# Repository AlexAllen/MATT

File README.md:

# Overview

MATT stands for "Multifunction Altimeter with Telemetry and Tracking", and is a DIY flight computer project that aims to tick several boxes in the [United Kingdom Rocketry Association's (UKRA) Model Achievement Program (MAP)](https://ukra.org.uk/certification/model-achievement-programme/). I have already done the DIY altimeter task, using an Arduino and breakout boards on stripboard, as recorded in [my rocket altimeter repo](https://github.com/AlexAllen/rocket_altimeter), and this project intends to produce something that can tick all of the remaining MAP tasks that require a custom altimeter:

* DIY flight computer
	* Details are light on the exact requirements, but I'm assuming a typical dual deploy flight computer
* Satellite
	* A cansat which records some physical data and transmits it back to the ground at 1Hz.
* Land under thrust
	* Need to be able to control servos for thrust vectoring

I also want to use this project as a vehicle for learning about PCB design, and to improve my electronics skills more generally. I intend to use a microcontroller board (maybe a Pico of some sort, or a Teensy) as a starting point, and then to create my own PCB to provide the rest of the functionality I require. I might do this in stages, creating some simpler boards with a subset of the final functionality on the way towards the final board. 

While the resulting flight computer will be overkill for any of these applications, as I don't expect space or weight contraints to be an issue for any of the flights (within reason), having them all use the same computer (or at least a subset of the same computer) means that every flight can help collect data and test functionality for each of the other applications. If I subsequently find I want a more compact, focussed flight computer for a specific application, then that can be its own project, building on the experience gained here. 

---------------------

# Requirements

1. Must have Mach safe two channel (apogee and main) deployment triggered off pressure data
	* Required to meet DIY flight computer task definition
1. Must have buzzer for audible altimeter arming alerts
	* Required for safety when completing DIY flight computer task
1. Must record flight data in a robust way in flight (not to an SD card!), and make the data retrievable afterwards
	* Will make the result more useful, and make it easier to test
1. Could have individual wireless test functionality for both deployment channels
	* Makes the result more flexible, but could be a later update
1. Must have UK legal radio link capable of transmitting recorded data at 1Hz
	* Required to meet Satellite task definition
1. Must record temperature data as well as pressure data, for transmission
	* Required for Satellite task
1. Should transmit on a frequency and in a format that can be picked up by an eggtimer USB ground station
	* Allows reuse of existing equiment
1. Must have enough PWM outputs to control a thrust vectoring mount and deploy legs
	* Required to meet the Land under thrust task task definition
1. Should have enough PWM outputs to control 4 canards instead of thrust vectoring and legs
	* Makes the result more future proof
1. Must have accelerometers and gyroscopes
	* Required to complete the Land under thrust task 
1. Should have magnetometers
	* Makes the result more flexible
1. Should have a GPS module, and be able to transmit as a GPS tracking radio
	* Makes the result more useful, given an onboard radio is required already
	
---------------------

# Potential chips/ boards to investigate

## Microcontroller

### Pimoroni Pico 2 Plus W / Pico LiPo 2 XL W

The Pico 2 Plus W was my starting point before I started looking at the Teensy alternatives. I already have some, and have used them at least a little, so that's a plus in their favour. They also either come with, or have options for coming with, some features I want already built in. This includes wifi, and some lipo functionality. It also has bluetooth, if I want to use that instead of wifi. 

The Pico LiPo 2 XL W has the lipo functionality built in already, and is longer as a result (76mm vs 51mm), but also comes with more pins. They are both 21mm wide.

Useful links:

* [Pimoroni Pico 2 Plus W](https://shop.pimoroni.com/products/pimoroni-pico-plus-2-w?variant=42182811942995)
* [Pimoroni LiPo Shim](https://shop.pimoroni.com/products/pico-lipo-shim?variant=32369543086163)
* [Pimoroni Pico LiPo 2 XL W](https://shop.pimoroni.com/products/pimoroni-pico-lipo-2-xl-w?variant=55447911006587)

### Teensy 4.0 or 4.1

This looks to have a significantly more powerful processor than a pico plus 2, and hardware floating point calculations, so I'll have plenty of grunt for calculations, but have to do more stuff myself (wifi, etc). The Teensy 4.1 is a larger and more fully featured board than the Teensy 4.0, at about 61mm vs 36mm (both are about 18mm wide). The 4.1 has the option to add 2x 8MB QSPI chips directly onto the board, and a built in microSD card reader, so I could look at writing some data storage/ retrival code before the PCB is complete.

Useful links:

* [Pi Hut Teensy 4.1](https://thepihut.com/products/teensy-4-1)
* [Pimoroni Teensy 4.1](https://shop.pimoroni.com/products/teensy-4-1?variant=31757218250835)
* [Teensy 4.1 documentation](https://www.pjrc.com/store/teensy41.html)

Or:

* [Pi Hut Teensy 4.0](https://thepihut.com/products/pjrc-teensy-4-0-usb-development-board)
* [Pimoroni Teensy 4.0](https://shop.pimoroni.com/products/teensy-4-0-development-board?variant=29443577217107)
* [Teensy 4.0 documentation](https://www.pjrc.com/store/teensy40.html)

## RF modules

### ESP8266-12 WiFi Module

If I go for the Teensy over the pico, then I don't get wifi built in. This is the wifi module that eggtimer uses.

### Hope RF HM-TRP-868 RF module

This is the one used by eggtimer, so should be compatible with the ground station. There is also an otherwise identical 433 MHz version, which may be useful later.

## Sensors

### BMP 390 (or 388, or 280, or ...)

A temperature and pressure sensor. I used the BMP 280 on my [rocket altimeter](https://github.com/AlexAllen/rocket_altimeter) with good results, and I have one on a breakout board to play with already. According to the Adafruit overview, the BMP280 has a relative accuracy of 12 Pa, the BMP388 8 Pa, and the BMP390 3 Pa. That translates to about 1m for the BMP280 or about 0.25m for the BMP390. Seems to be recommended on TRF threads about building flight computers, so this is probably the one to go for.

### LSM6DSV80X 

A two channel accelerometer, with gyroscope. 16g and 80g should cover most foreseeable use cases. The LSM6DSO32 or similar seem to be recommended on TRF, but this looks like an updated version that includes an 80g rather than a 32g high range accelerometer.

### LIS3MDL

This magnetometer is discussed on [TRF](https://www.rocketryforum.com/threads/magnetometer-calibration.193930/), but seems to be unavailable.

### LIS2MDLTR

This does appear to be available.

### Quectel L80-R

I have some of these, somewhere. Which is a big point in their favour!

### Something from ublox?

People seem to rate these highly, might be worth investigating

## Other

### VN5E160STR-E

These are what the eggtimer quark uses to control deployment charges. According to Cris Erving of Eggtimer Rocketry, ["in one SOIC-8 package you get 10A current limiting, continuity checking, brownout protection (it shuts off the load if the input voltage drops below 4.5V), overtemperature protection, and they will work with up to 40V input."](https://www.rocketryforum.com/threads/flight-computer-schematic-review-request.186506/post-2588670).

### W25Q01JVZEIM 

1 gigabit flash, so could store plenty of flight data, and recover it later, even after power off.

### Pololu D30V30MAL

Looks like a very capable buck converter.
	
---------------------

# Other useful things:

### Ulyu (Silicdyne) talks about how to implement an IMU

[This thread on TRF](https://www.rocketryforum.com/threads/did-any-one-found-out-a-way-to-calculate-the-velocity-and-altitude-using-imu-sensors-with-practical-code.191467/post-2722289)

### Cris Erving (Eggtimer) suggests owning this book

[The Circuit Designer's Companion](https://www.amazon.co.uk/Circuit-Designers-Companion-Wilson-Professor/dp/0081017642)

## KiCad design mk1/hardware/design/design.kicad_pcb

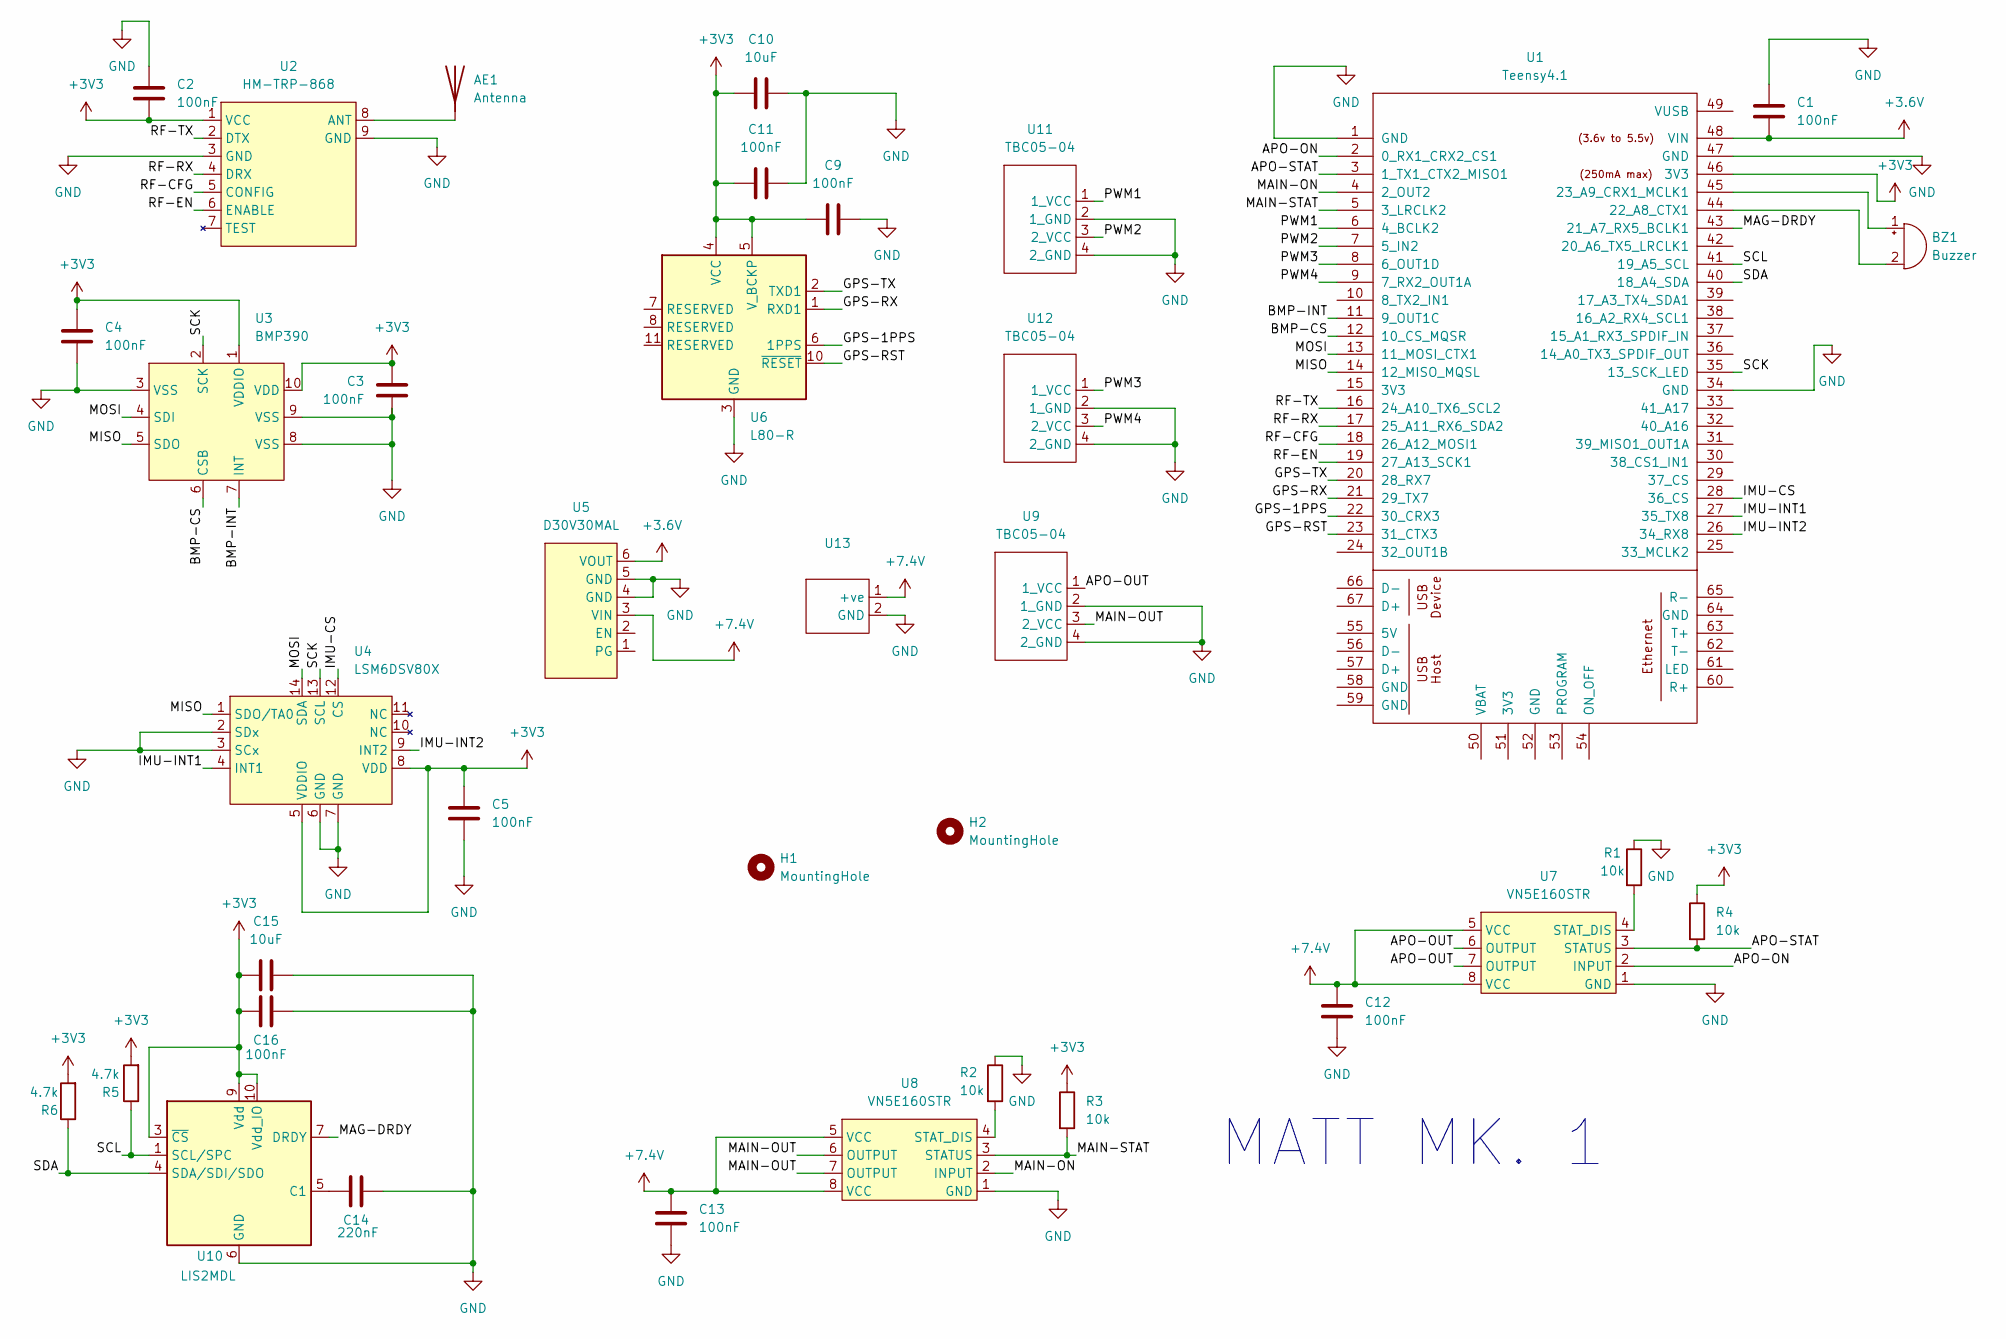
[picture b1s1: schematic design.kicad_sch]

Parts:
AE1: Antenna; ANT-868-PW
BZ1: Buzzer; AX1203DLF
C1, C2, C3, C4, C5, C9, C11, C12, C13, C16: 100nF; C_0805_2012Metric_Pad1.18x1.45mm_HandSolder
C10, C15: 10uF; C_0805_2012Metric_Pad1.18x1.45mm_HandSolder
C14: 220nF; C_0805_2012Metric_Pad1.18x1.45mm_HandSolder
H1, H2: MountingHole; MountingHole_2.7mm_M2.5
R1, R2, R3, R4: 10k; R_0805_2012Metric_Pad1.20x1.40mm_HandSolder
R5, R6: 4.7k; R_0805_2012Metric_Pad1.20x1.40mm_HandSolder
U1: Teensy4.1; teensy4.1
U2: HM-TRP-868; HM-TRP-XXX
U3: BMP390
U4: LSM6DSV80X
U5: D30V30MAL; D30V30MAx
U6: L80-R; Quectel_L80-R
U7, U8: VN5E160STR; vn5e160s
U9: TBC05-04; TBC05-04_charges
U10: LIS2MDL; LGA-12_2x2mm_P0.5mm
U11: TBC05-04; TBC05-04_pwm1
U12: TBC05-04; TBC05-04_pwm2
U13: power_in

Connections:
+3.6V: C1.1, U1.48 (VIN), U5.6 (VOUT)
+3V3: C2.2, C3.1, C4.1, C5.1, C9.2, C10.2, C11.2, C15.1, C16.2, R3.1, R4.1, R5.2, R6.2, U1.46 (3V3), U2.1 (VCC), U3.1 (VDDIO), U3.10 (VDD), U4.5 (VDDIO), U4.8 (VDD), U6.4 (VCC), U6.5 (V_BCKP), U10.3 (~CS), U10.9 (Vdd), U10.10 (Vdd_IO)
+7.4V: C12.1, C13.1, U5.3 (VIN), U7.5 (VCC), U7.8 (VCC), U8.5 (VCC), U8.8 (VCC), U13.1 (+ve)
/APO-ON: U1.2 (0_RX1_CRX2_CS1), U7.2 (INPUT)
/APO-OUT: U7.6 (OUTPUT), U7.7 (OUTPUT), U9.1 (1_VCC)
/APO-STAT: R4.2, U1.3 (1_TX1_CTX2_MISO1), U7.3 (STATUS)
/BMP-CS: U1.12 (10_CS_MQSR), U3.6 (CSB)
/BMP-INT: U1.11 (9_OUT1C), U3.7 (INT)
/GPS-1PPS: U1.22 (30_CRX3), U6.6 (1PPS)
/GPS-RST: U1.23 (31_CTX3), U6.10 (~RESET)
/GPS-RX: U1.21 (29_TX7), U6.1 (RXD1)
/GPS-TX: U1.20 (28_RX7), U6.2 (TXD1)
/IMU-CS: U1.28 (36_CS), U4.12 (CS)
/IMU-INT1: U1.27 (35_TX8), U4.4 (INT1)
/IMU-INT2: U1.26 (34_RX8), U4.9 (INT2)
/MAG-DRDY: U1.43 (21_A7_RX5_BCLK1), U10.7 (DRDY)
/MAIN-ON: U1.4 (2_OUT2), U8.2 (INPUT)
/MAIN-OUT: U8.6 (OUTPUT), U8.7 (OUTPUT), U9.3 (2_VCC)
/MAIN-STAT: R3.2, U1.5 (3_LRCLK2), U8.3 (STATUS)
/MISO: U1.14 (12_MISO_MQSL), U3.5 (SDO), U4.1 (SDO/TA0)
/MOSI: U1.13 (11_MOSI_CTX1), U3.4 (SDI), U4.14 (SDA)
/PWM1: U1.6 (4_BCLK2), U11.1 (1_VCC)
/PWM2: U1.7 (5_IN2), U11.3 (2_VCC)
/PWM3: U1.8 (6_OUT1D), U12.1 (1_VCC)
/PWM4: U1.9 (7_RX2_OUT1A), U12.3 (2_VCC)
/RF-CFG: U1.18 (26_A12_MOSI1), U2.5 (CONFIG)
/RF-EN: U1.19 (27_A13_SCK1), U2.6 (ENABLE)
/RF-RX: U1.17 (25_A11_RX6_SDA2), U2.4 (DRX)
/RF-TX: U1.16 (24_A10_TX6_SCL2), U2.2 (DTX)
/SCK: U1.35 (13_SCK_LED), U3.2 (SCK), U4.13 (SCL)
/SCL: R5.1, U1.41 (19_A5_SCL), U10.1 (SCL/SPC)
/SDA: R6.1, U1.40 (18_A4_SDA), U10.4 (SDA/SDI/SDO)
GND: C1.2, C2.1, C3.2, C4.2, C5.2, C9.1, C10.1, C11.1, C12.2, C13.2, C14.2, C15.2, C16.1, R1.1, R2.1, U1.1 (GND), U1.34 (GND), U1.47 (GND), U2.3 (GND), U2.9 (GND), U3.3 (VSS), U3.8 (VSS), U3.9 (VSS), U4.2 (SDx), U4.3 (SCx), U4.6 (GND), U4.7 (GND), U5.4 (GND), U5.5 (GND), U6.3 (GND), U6.12 (GND), U7.1 (GND), U8.1 (GND), U9.2 (1_GND), U9.4 (2_GND), U10.6 (GND), U10.8 (GND), U11.2 (1_GND), U11.4 (2_GND), U12.2 (1_GND), U12.4 (2_GND), U13.2 (GND)
unnamed: AE1.1 (A), U2.8 (ANT)
unnamed: BZ1.1 (+), U1.45 (23_A9_CRX1_MCLK1)
unnamed: BZ1.2 (-), U1.44 (22_A8_CTX1)
unnamed: R1.2, U7.4 (STAT_DIS)
unnamed: R2.2, U8.4 (STAT_DIS)
unnamed: C14.1, U10.5 (C1)

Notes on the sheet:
MATT MK. 1

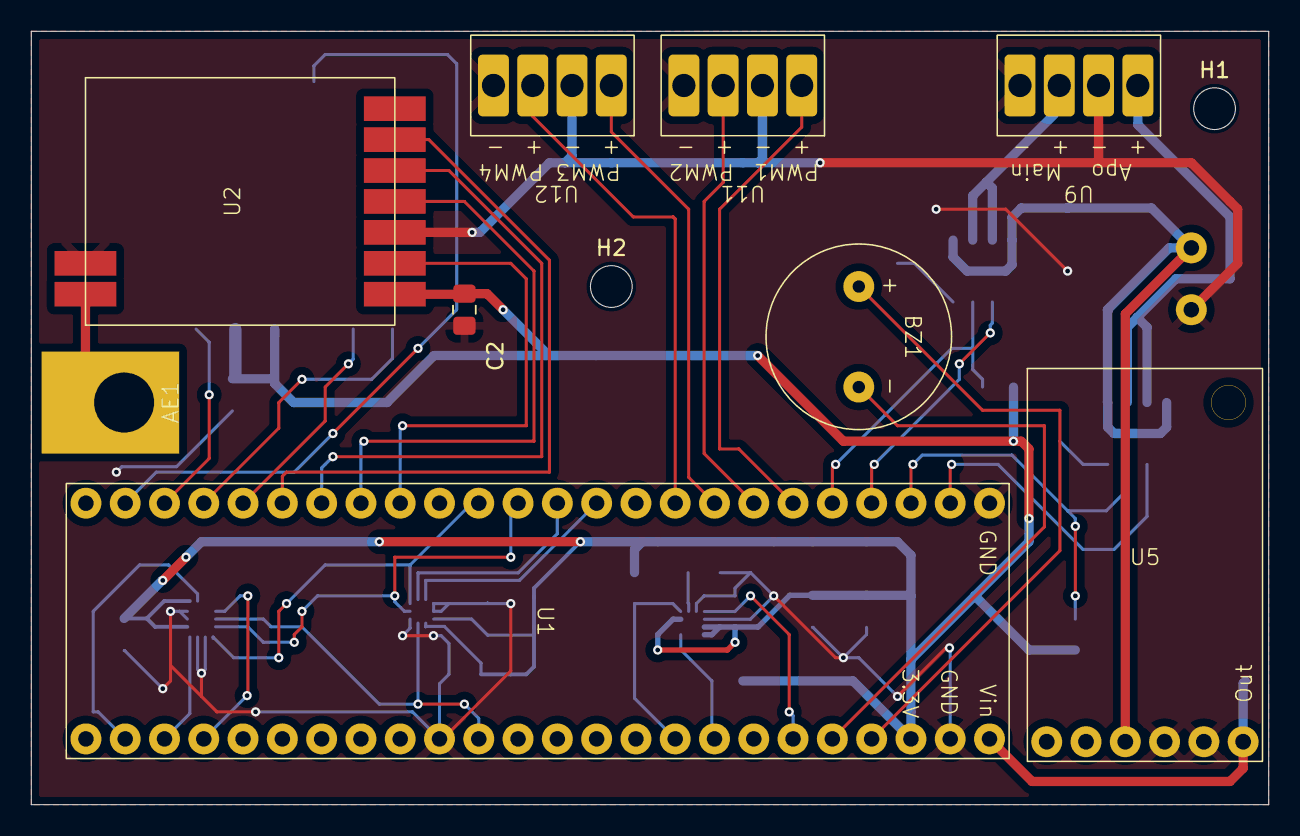
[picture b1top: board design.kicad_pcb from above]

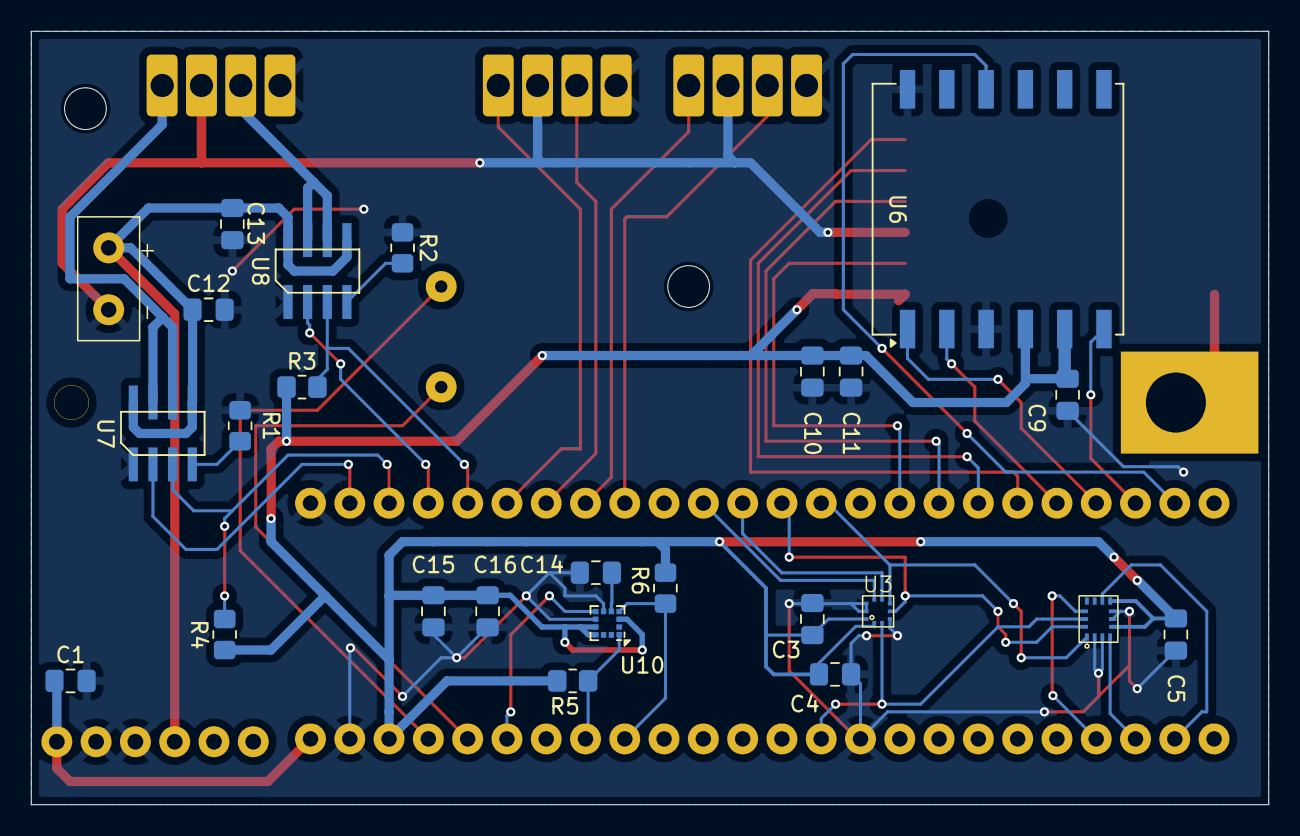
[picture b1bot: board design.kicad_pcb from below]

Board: 2 copper layers, 80.0 x 50.0 mm, 36 parts (25 on the bottom side), 39 nets.

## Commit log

2025-12-10 Added readme file, with some initial thoughts
2025-12-17 Added some more thoughts on microcontrollers
2025-12-17 Added additional requirements, and updated overview to include incremental progress towards the full computer
2025-12-18 Added some more notes
2025-12-20 Add magnetometer to readme
2025-12-20 Update RF module details
2025-12-26 Add mk1 board schematic
2025-12-30 Remove lock file
2025-12-30 Remove other temporary file
2025-12-30 Updated schematic to use different (available) magnetometer
2025-12-30 Update documentation
2025-12-31 Added symbol table, fixed magnetometer wiring
2026-01-01 Added footprints
2026-01-02 Add BOM and make a start at giving everything a suitable footprint
2026-01-03 Picked antenna for BOM and added footprint
2026-01-03 Add a few missing in and outputs, try to join up pins
2026-01-07 First pass at PCB
2026-01-07 Close kicad before committing!
2026-01-07 Increase voltage regulator pad size
2026-01-08 Added mounting holes
2026-01-12 Thickened power traces, and tidied up a few sections. Still a bunch of design rule errors to work through
2026-01-18 Fixed errors and some warnings
